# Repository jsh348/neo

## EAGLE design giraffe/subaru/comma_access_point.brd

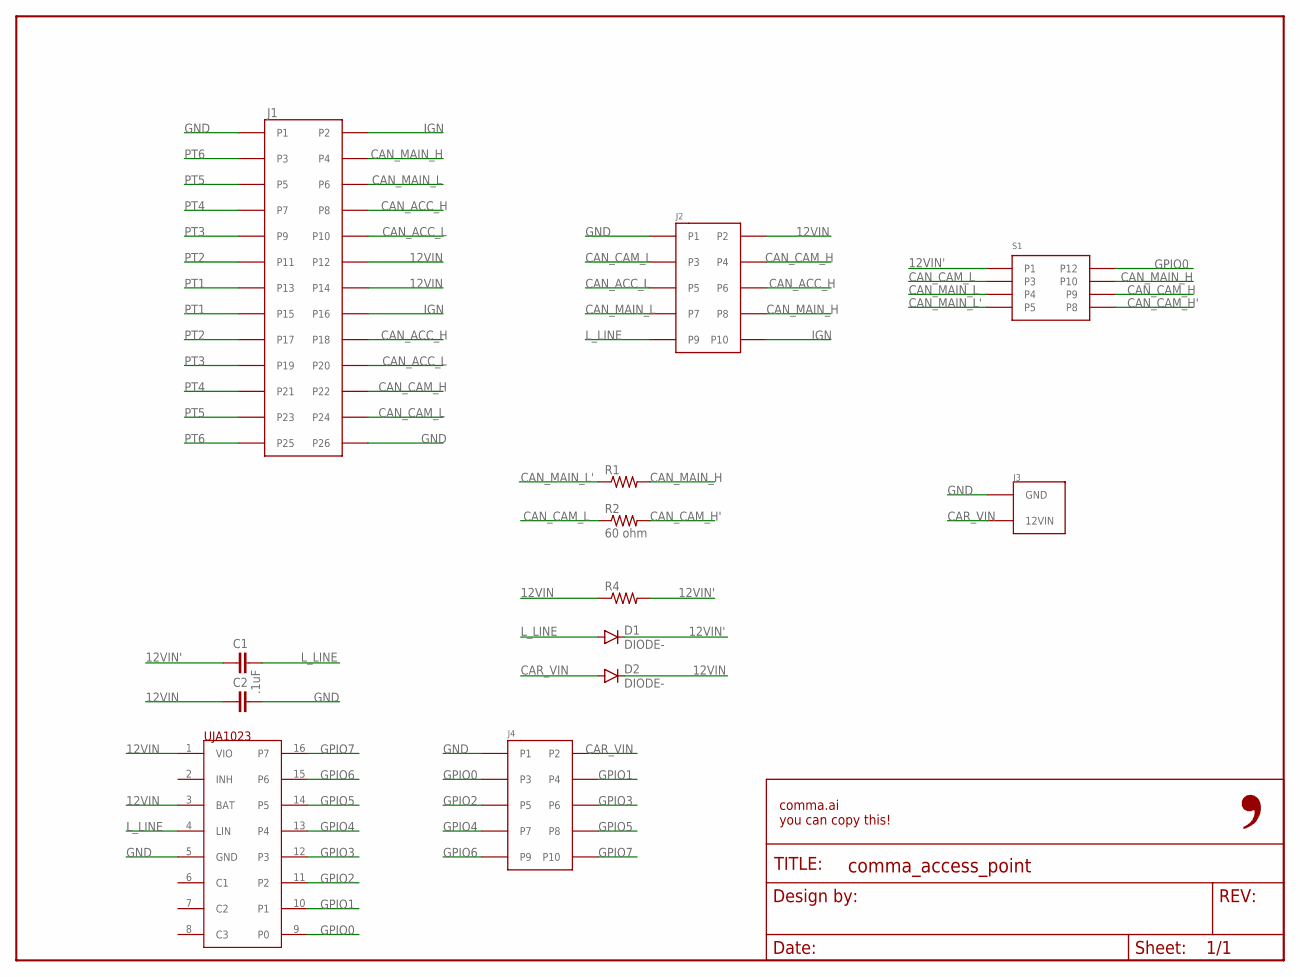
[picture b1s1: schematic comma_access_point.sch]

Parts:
C1: C0805; 0805-C
C2: .1uF; 0805-C
D1, D2: DIODE-; DO-214
FRAME1: FRAME-LETTER-OPENNO_PACKAGE; DUMMY
IC1: UJA1023; SO16
J1: 5018762640
J2, J4: 5018761040
J3: 3-794618-2
R1, R4: R0402; 0402-R
R2: 60 ohm; 0402-R
S1: G6S-2G-DC12; G6S-26-DC12

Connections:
12VIN: C2.1, D2.1 (C), IC1.1 (VIO), IC1.3 (BAT), J1.P12, J1.P14, J2.P2, R4.1
12VIN': C1.1, D1.1 (C), R4.2, S1.P1
CAN_ACC_H: J1.P8, J1.P18, J2.P6
CAN_ACC_L: J1.P10, J1.P20, J2.P5
CAN_CAM_H: J1.P22, J2.P4, S1.P9
CAN_CAM_H': R2.2, S1.P8
CAN_CAM_L: J1.P24, J2.P3, R2.1, S1.P3
CAN_MAIN_H: J1.P4, J2.P8, R1.2, S1.P10
CAN_MAIN_L: J1.P6, J2.P7, S1.P4
CAN_MAIN_L': R1.1, S1.P5
CAR_VIN: D2.2 (A), J3.12VIN, J4.P2
GND: C2.2, IC1.5 (GND), J1.P1, J1.P26, J2.P1, J3.GND, J4.P1
GPIO0: IC1.9 (P0), J4.P3, S1.P12
GPIO1: IC1.10 (P1), J4.P4
GPIO2: IC1.11 (P2), J4.P5
GPIO3: IC1.12 (P3), J4.P6
GPIO4: IC1.13 (P4), J4.P7
GPIO5: IC1.14 (P5), J4.P8
GPIO6: IC1.15 (P6), J4.P9
GPIO7: IC1.16 (P7), J4.P10
IGN: J1.P2, J1.P16, J2.P10
L_LINE: C1.2, D1.2 (A), IC1.4 (LIN), J2.P9
PT1: J1.P13, J1.P15
PT2: J1.P11, J1.P17
PT3: J1.P9, J1.P19
PT4: J1.P7, J1.P21
PT5: J1.P5, J1.P23
PT6: J1.P3, J1.P25

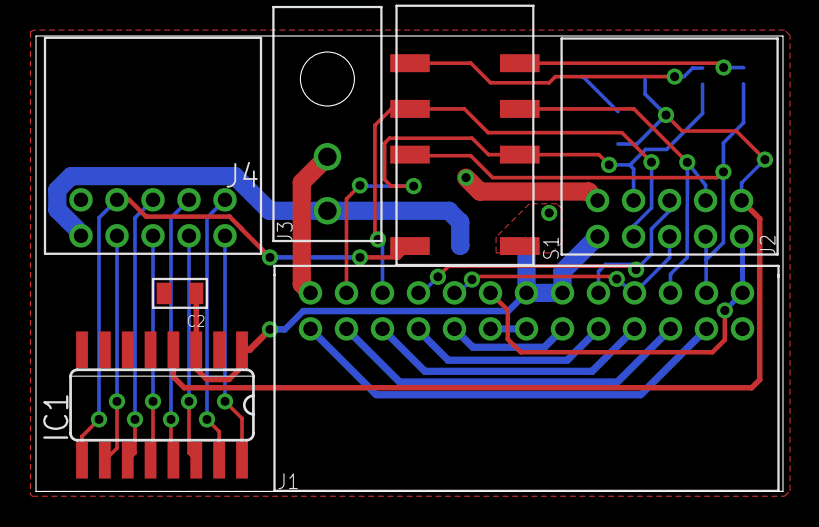
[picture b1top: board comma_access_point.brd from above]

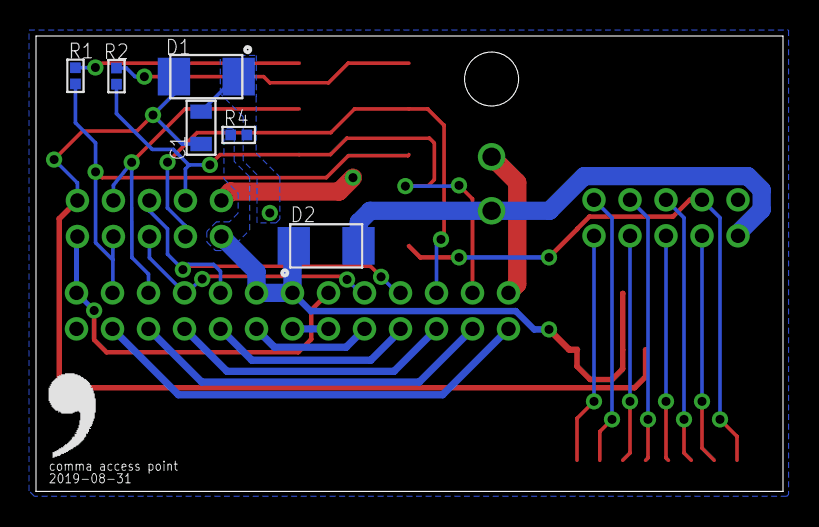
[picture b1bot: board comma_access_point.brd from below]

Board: 2 copper layers, 41.5 x 25.3 mm, 15 parts (7 on the bottom side), 28 nets.

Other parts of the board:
U$1: LOGO

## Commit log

2019-08-31 added UJA1023 to subaru giraffe on mlp's request
